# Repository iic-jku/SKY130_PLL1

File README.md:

# pll2022
Implementation of a Sub-Sampling PLL targeting SerDes Applications
__________________________________________________________________

Submission(s) for precheck - 31.08.2022:
> folder "PICO Contest"
> includes Pin List as well as "pin dummy"(dummy project but with all the correct pins)

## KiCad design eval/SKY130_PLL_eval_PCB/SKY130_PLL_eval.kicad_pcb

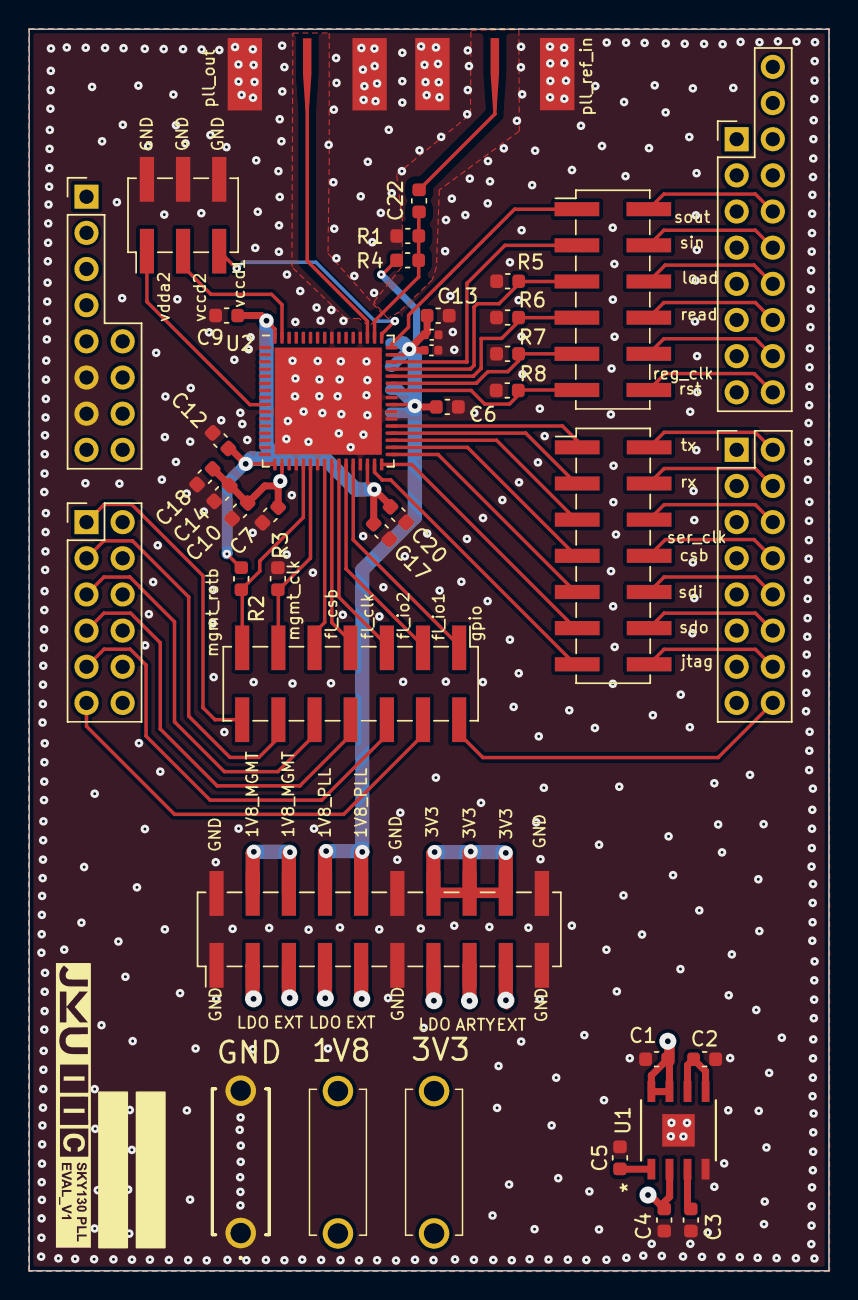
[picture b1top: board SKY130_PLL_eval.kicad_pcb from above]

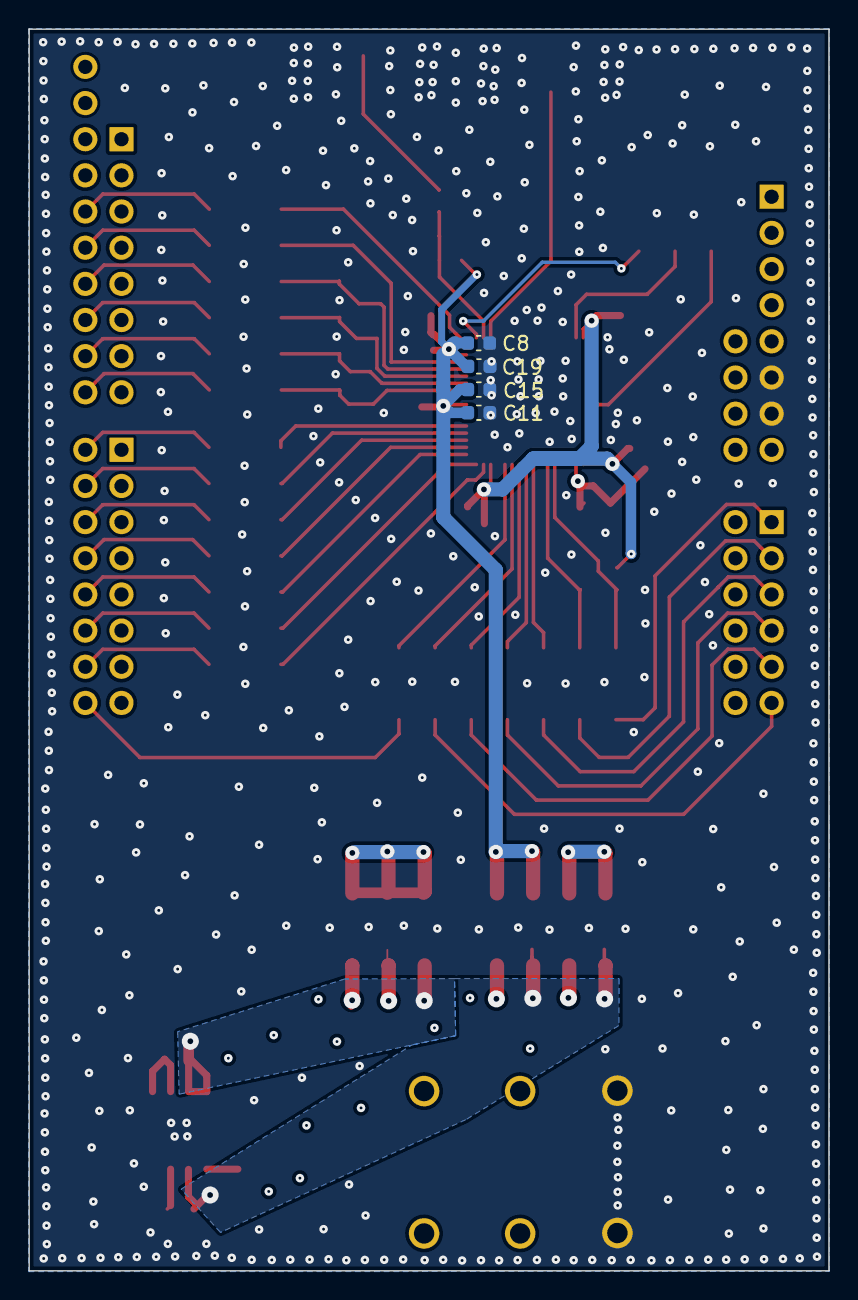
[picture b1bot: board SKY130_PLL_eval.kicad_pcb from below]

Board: 4 copper layers, 56.2 x 87.2 mm, 43 parts (4 on the bottom side), 58 nets.

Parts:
C1, C4, C5, C7, C8, C9: 10u; C_0603_1608Metric
C2, C3, C14, C15, C17: 1u; C_0603_1608Metric
C6: 10n; C_0603_1608Metric
C10, C11, C12: 4.7u; C_0603_1608Metric
C13, C22: 1n; C_0603_1608Metric
C16: 82p; C_0402_1005Metric
C18, C19, C20: 100n; C_0603_1608Metric
C21: 68p; C_0402_1005Metric
J1: Conn_02x10_Odd_Even; PinHeader_2x10_P2.54mm_Vertical_SMD
J2: Conn_02x03_Odd_Even; PinHeader_2x03_P2.54mm_Vertical_SMD
J3, J5: Conn_02x07_Odd_Even; PinHeader_2x07_P2.54mm_Vertical_SMD
J6: Conn_02x06_Odd_Even; PinHeader_2x06_P2.54mm_Vertical_SMD
J_PLL_OUT1: 142-0701-851_TO_SENSO1
J_PLL_REF_IN1: 142-0701-851_TO_SENSO1
R1, R4: 100; C_0603_1608Metric
R2, R3, R5, R6, R7, R8: 100k; C_0603_1608Metric
TP1V8, TP3V3: Mini_Banana_Plug_Red; 930224101
TPGND1: Mini_Banana_Plug_Black; 930224100
U1: ADM7154ARDZ-1.8-R7; RD-8-1_ADI
U2: Caravel_QFN; QFN-64-1EP_9x9mm_P0.5mm_EP7.65x7.65mm
XA1: Arty_A7_Shield

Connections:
/IC_Packaged/flash_clk: J3.7, U2.25 (flash_clk)
/IC_Packaged/flash_csb: J3.9, U2.24 (flash_csb)
/IC_Packaged/flash_io1: J3.3, U2.27 (flash_io1)
/IC_Packaged/flash_io2: J3.5, U2.26 (flash_io0)
/IC_Packaged/gpio: J3.1, U2.28 (gpio)
/IC_Packaged/mgmt_clk: J3.11, R3.1, U2.22 (clock)
/IC_Packaged/mgmt_rstb: J3.13, R2.2, U2.21 (resetb)
/IC_Packaged/pll_load: J6.5, R5.1, U2.45 (mprj_io[11])
/IC_Packaged/pll_read: J6.7, R6.1, U2.44 (mprj_io[10])
/IC_Packaged/pll_reg_clk_in: J6.9, R7.1, U2.43 (mprj_io[9])
/IC_Packaged/pll_reset: J6.11, R8.1, U2.42 (mprj_io[8])
/IC_Packaged/pll_sin: J6.3, U2.46 (mprj_io[12])
/IC_Packaged/pll_sout: J6.1, U2.48 (mprj_io[13])
/IC_Packaged/ser_clk: J5.5, U2.35 (mprj_io[4]_SCK)
/IC_Packaged/ser_csb: J5.7, U2.34 (mprj_io[3]_CSB)
/IC_Packaged/ser_jtag: J5.13, U2.31 (mprj_io[0]_JTAG)
/IC_Packaged/ser_rx: J5.3, U2.36 (mprj_io[5]_ser_rx)
/IC_Packaged/ser_sdi: J5.9, U2.33 (mprj_io[2]_SDI)
/IC_Packaged/ser_sdo: J5.11, U2.32 (mprj_io[1]_SDO)
/IC_Packaged/ser_tx: J5.1, U2.37 (mprj_io[6]_ser_tx)
/IC_Packaged/vccd1: J2.5, U2.49 (vccd1)
/IC_Packaged/vccd2: J2.3, U2.63 (vccd2)
/IC_Packaged/vdda2: J2.1, U2.9 (vdda2)
/PLL_IO/pll_sma_in: C22.1, J_PLL_REF_IN1.1
/Power/LDO_BYP: C3.1, U1.3 (BYP)
/Power/LDO_REF: C2.1, U1.5 (REF_SENSE), U1.6 (REF)
/Power/LDO_VREG: C5.1, U1.1 (VREG)
/Power/VDD_1V8_EXT: J1.5, J1.9, TP1V8.1, TP1V8.2
/Power/VDD_1V8_LDO: C4.1, J1.3, J1.7, U1.2 (VOUT)
/Power/VDD_3V3_EXT: J1.17, TP3V3.1, TP3V3.2
/Power/VDD_3V3_LDO: C1.1, J1.13, U1.7 (EN), U1.8 (VIN)
GND: C1.2, C2.2, C3.2, C4.2, C5.2, C6.2, C7.2, C8.2, C9.2, C10.2, C11.2, C12.2, C13.2, C14.2, C15.2, C16.2, C17.2, C18.2, C19.2, C20.2, C21.2, J1.1, J1.2, J1.11, J1.12, J1.19, J1.20, J2.2, J2.4, J2.6, J_PLL_OUT1.2, J_PLL_OUT1.3, J_PLL_REF_IN1.2, J_PLL_REF_IN1.3, R1.2, R3.2, R5.2, R6.2, R7.2, R8.2, TPGND1.1, TPGND1.2, U1.4 (GND), U1.9 (GND), U2.1 (vssa2), U2.10 (vssd2), U2.20 (vssa), U2.23 (vssd), U2.29 (vssio), U2.38 (vssa1), U2.39 (vssd1), U2.41 (mprj_io[7]), U2.52 (vssa1), U2.56 (vssio), U2.65 (ThermalPad), XA1.GND0 (GND), XA1.GND1 (GND)
VDD_1V8_MGMT: C7.1, C10.1, C14.1, C18.1, J1.4, J1.6, U2.18 (vccd)
VDD_1V8_PLL: C6.1, C8.1, C11.1, C13.1, C15.1, C16.1, C19.1, C21.1, J1.8, J1.10, R4.1, U2.40 (vdda1), U2.47 (vdda1)
VDD_3V3: C9.1, C12.1, C17.1, C20.1, J1.14, J1.16, J1.18, R2.1, U2.17 (vddio), U2.30 (vdda), U2.64 (vddio)
VDD_3V3_ARTY: J1.15, XA1.3V3 (3.3V)
flash_clk_arty: J3.8, XA1.A3
flash_csb_arty: J3.10, XA1.A2
flash_io1_arty: J3.4, XA1.A5
flash_io2_arty: J3.6, XA1.A4
gpio_arty: J3.2, XA1.IO0
mgmt_clk_arty: J3.12, XA1.A1
mgmt_rstb_arty: J3.14, XA1.A0
pll_load_arty: J6.6, XA1.IO11
pll_out: J_PLL_OUT1.1, U2.51 (mprj_io[15])
pll_read_arty: J6.8, XA1.IO10
pll_ref_in: C22.2, R1.1, R4.2, U2.50 (mprj_io[14])
pll_reg_clk_in_arty: J6.10, XA1.IO9
pll_reset_arty: J6.12, XA1.IO8
pll_sin_arty: J6.4, XA1.IO12
pll_sout_arty: J6.2, XA1.IO13
ser_clk_arty: J5.6, XA1.IO5
ser_csb_arty: J5.8, XA1.IO4
ser_jtag_arty: J5.14, XA1.IO1
ser_rx_arty: J5.4, XA1.IO6
ser_sdi_arty: J5.10, XA1.IO3
ser_sdo_arty: J5.12, XA1.IO2
ser_tx_arty: J5.2, XA1.IO7

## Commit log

2022-07-06 first upload
2022-07-19 PICO presentation
2022-07-20 symbols+new simulation
2022-08-09 layouts+pics+simulations
2022-08-23 add pin list for mock-tapeout
2022-08-29 solve conflict
2022-08-30 update SSCS Pin List
2022-08-31 precheck
2022-09-25 cleanup+organizing
    created a new file structure and added all relevant files again
2022-09-29 create design review ppt
2022-09-30 update design review
2022-10-23 update files
2022-11-11 file update
2022-11-11 added wrapper
2022-11-13 first final round
2022-11-14 lvs+gds update
2022-11-28 lvs+gds update 2
2024-03-18 Chip pinout and caravel layout
2024-04-05 PCB v1 added
2024-04-08 eval pcb added
2024-04-08 pin header labeling inserted
2024-04-09 labels updated
2024-04-09 minor layout changes
2024-04-09 version updated to Kicad 8.0
2024-04-23 digital design evaluation added
2024-04-23 evaluation of digital part added
